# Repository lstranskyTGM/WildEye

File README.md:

# WildEye

WIldEye Wildkamera Diplomprojekt

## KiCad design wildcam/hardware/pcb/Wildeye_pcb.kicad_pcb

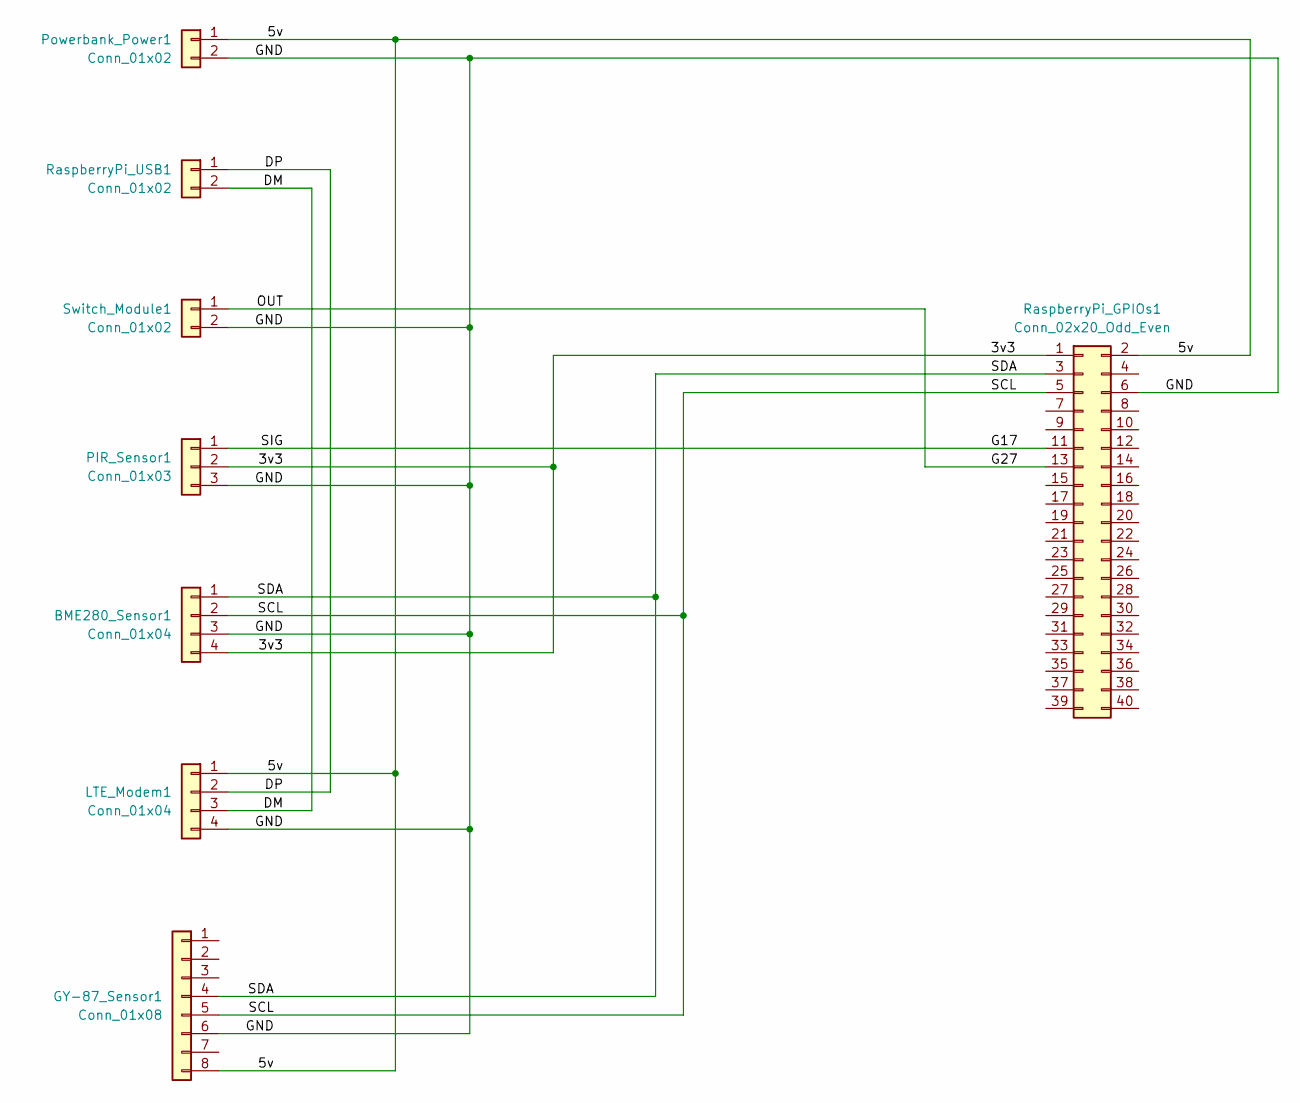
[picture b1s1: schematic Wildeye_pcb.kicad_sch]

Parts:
BME280_Sensor1: Conn_01x04; PinHeader_1x04_P2.54mm_Vertical
GY-87_Sensor1: Conn_01x08; PinHeader_1x08_P2.54mm_Vertical
LTE_Modem1: Conn_01x04; PinHeader_1x04_P2.54mm_Vertical
PIR_Sensor1: Conn_01x03; PinHeader_1x03_P2.54mm_Vertical
Powerbank_Power1: Conn_01x02; PinHeader_1x02_P2.54mm_Vertical
RaspberryPi_GPIOs1: Conn_02x20_Odd_Even; PinHeader_2x20_P2.54mm_Vertical
RaspberryPi_USB1: Conn_01x02; PinHeader_1x02_P2.54mm_Vertical
Switch_Module1: Conn_01x02; PinHeader_1x02_P2.54mm_Vertical

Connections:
/3v3: BME280_Sensor1.4, PIR_Sensor1.2, RaspberryPi_GPIOs1.1
/5v: GY-87_Sensor1.8, LTE_Modem1.1, Powerbank_Power1.1 (5V), RaspberryPi_GPIOs1.2
/DM: LTE_Modem1.3, RaspberryPi_USB1.2
/DP: LTE_Modem1.2, RaspberryPi_USB1.1
/G17: PIR_Sensor1.1, RaspberryPi_GPIOs1.11
/G27: RaspberryPi_GPIOs1.13, Switch_Module1.1
/GND: BME280_Sensor1.3, GY-87_Sensor1.6, LTE_Modem1.4, PIR_Sensor1.3, Powerbank_Power1.2 (GND), RaspberryPi_GPIOs1.6, Switch_Module1.2
/SCL: BME280_Sensor1.2, GY-87_Sensor1.5, RaspberryPi_GPIOs1.5
/SDA: BME280_Sensor1.1, GY-87_Sensor1.4, RaspberryPi_GPIOs1.3

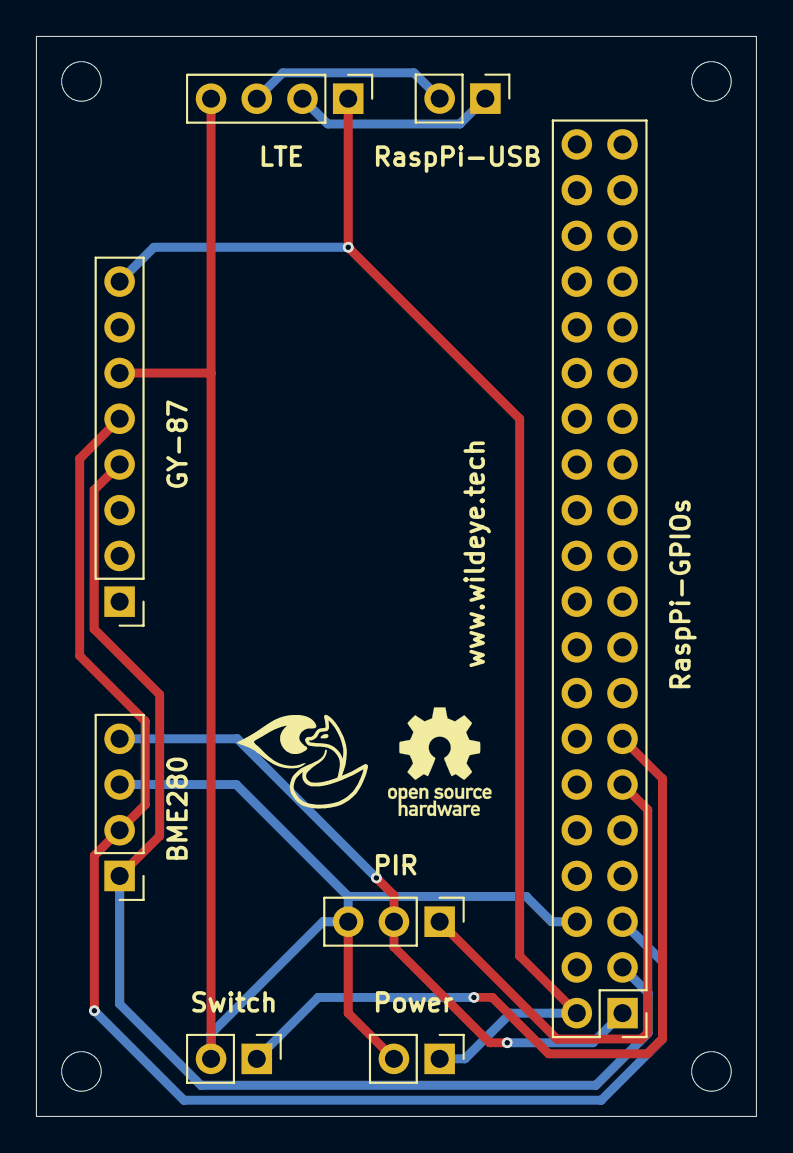
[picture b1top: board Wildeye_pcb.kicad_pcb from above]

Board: 2 copper layers, 40.0 x 60.0 mm, 12 parts (0 on the bottom side), 9 nets.

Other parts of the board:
REF1, REF2, REF3, REF4: MountingHole_2.2mm_M2

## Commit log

2024-09-30 upated ReadMe.md
2024-09-30 added project representation website v1
2024-10-04 added main website
2024-10-04 added dashboard v1
2024-10-04 fixed dependency issues
2024-10-07 slightly changed layout, disabled zoom control for map.
2024-10-08 added add camera button and modal, edit icon, slight layout changes
2024-10-16 Add project directories and placeholder files
2024-10-18 Revise project folder structure
2024-10-18 Unify .gitignore files
2024-10-21 Create test_bme280_sensor.py for temperature, humidity, and pressure data
2024-10-22 Create test_bh1750_sensor.py for light intensity data
2024-10-23 Switch test_bme280_sensor.py to smbus from busio
2024-10-23 Switch test_pir_sensor.py to RPi.GPIO library from gpiozero
2024-10-23 Enhance test_camera_module.py with improved error handling and modular design
2024-10-23 Misc: update code style and comments
2024-10-23 Create LICENSE
2024-10-24 changed layout slightly, changed names to be more consistent.
2024-10-24 added updates for current status
2024-10-25 Create test_ds3231.py for reading and setting time
2024-10-26 Improve test_pir_sensor.py overall error handling
2024-10-26 Enhance: improve error handling across all test scripts
2024-10-26 Modify test_ds3231_rtc.py set_time conversion logic
2024-10-28 Resolve naming issue in test_bh1750_sensor.py
2024-10-29 Create test_mpu6050_sensor.py for accelerometer and gyroscope data
2024-10-30 Create test_flask_app/ for Flask-based configuration interface
2024-11-01 Misc: add error prints, rename vars, PEP8 fixes, remove .gitkeep
2024-11-03 Create folder structure for test scripts
2024-11-07 Create test_background_subtraction.py for presence detection
2024-11-08 added random pixabay pictures, new logo
2024-11-13 new logo
2024-11-13 added v1 of api design
2024-11-14 small change to api
2024-11-19 Strapi Prototyping
2024-11-26 added new news to news section
2024-11-27 Remove test_background_subtraction.py: not used
2024-11-29 added material web components, css variables.
2024-12-01 Create test_lte_modem.py for AT command interface
2024-12-02 Changed Dashboard to match material design mockup.
2024-12-03 Create test_optical_flow.py for motion detection
2024-12-04 changed title and favicon, changed MapView to match Mockup.
2024-12-04 Notes for AI
2024-12-04 Remove test_bh1750_sensor.py: not used
2024-12-04 Remove .gitkeep
2024-12-05 account view
2024-12-08 Mac projekt hinzu gefügt
2024-12-08 Create settings.md for configuration options
2024-12-09 changed AccountView.vue, added CameraComponent.vue stuff
2024-12-09 Modify settings.md: updated variable names and datatypes for consistency
2024-12-11 Projektwebsite v2 fertig
2024-12-12 updated marker popup component to new material design
2024-12-13 Neues Update
2024-12-13 Erstellen des Diagrammes des neuronaln Netwerkes.
2024-12-13 Modify wildcam.conf: add settings for device configuration
2024-12-13 Create network.conf for LTE and server connection settings
2024-12-19 added new color schemes, temp dialog eventually used for settings and camera-code input
2024-12-19 small api design update, advanced settings dialog added
2024-12-31 Move test_pir_sensor.py to detection folder
2024-12-31 Rename test_lte_modem.py to test_lte_at.py
2024-12-31 Create test_lte_gps.py for GPS location retrieval
2025-01-01 Modify test_pir_sensor.py: modularize, simplify, fix interrupts
2025-01-02 Modify test_bme280_sensor.py: implement class, add logging, improve documentation
2025-01-03 Modify test_mpu6050_sensor.py: implement class/library, add logging, improve documentation
2025-01-03 Remove test_ds3231_rtc.py: critical functionality issues, not feasible to fix
2025-01-05 Create test_http_request.py for HTTP requests over LTE
2025-01-08 small design updates
2025-01-08 added popout image viewer
2025-01-08 small design changes in the account view
2025-01-09 small design and layout changes throughout whole website
2025-01-10 started implementing future API, currently using development test server with default values
2025-01-11 added new API functionality, changed layout of settings popups.
2025-01-14 added new updates, portraits, changes milestone completion
2025-01-14 css updates for projektwebseite
2025-01-14 datum geändert auf heutiges
2025-01-19 added login, logout procedure, cookies for session storage.
2025-01-19 additional session logic, small design updates
2025-01-20 added docker and new leo bild
2025-01-22 updated api design, small changes in code to adapt.
2025-01-22 added flask api server to git
2025-01-23 Add STL files for prototype to wildcam/hardware/3d_models folder
2025-01-27 Fix docker-compose.yml: add restart policy
2025-02-11 updated project website
2025-02-11 changed image to a cc image.
2025-02-17 Move manual test scripts to /scripts/tests/manual/
2025-02-17 Create README.md
    An API documentation V1
2025-02-17 small format changes to README.md
2025-02-17 Update README.md
    fixed typos in requests
2025-02-18 updated logo, api now works for login and getCameras
2025-02-18 replaced camera quick info with actual info from api
2025-02-18 added code for carousel of standard and AI analyzed image, replaced logo with new version
2025-02-18 Create base_module.py: abstract base class for hardware modules
2025-02-19 Create media/ folder structure for storing captured data
2025-02-19 Create camera_module.py: implement image & video capture
2025-02-20 Modify base_module.py: add type hinting
2025-02-20 Fix camera_module.py: ensure camera stops after recording
2025-02-21 Modify base_module.py: improve docs & remove unused read_data method
2025-02-21 Modify camera_module.py: refine docs & cleanup method
2025-02-21 Create pir_sensor.py: handle motion detection using GPIO
2025-02-23 Modify docstring formatting for scripts under /hardware
2025-02-23 Refactor initialize to hardware_setup & update wrapper calls for clarity
2025-02-23 Modify generate_file_path in camera_module.py to be private for internal use
2025-02-23 Create event_handler.py: handle motion events & trigger media capture
2025-02-24 new updates for project website
2025-02-24 Fix event_handler.py: resolve TypeError by correcting handle_motion_event parameter
2025-02-24 Refactor event_handler.py: move record_type to init as a temporary fixed value
2025-02-24 Modify event_handler.py: enhance docstrings & define future methods
2025-02-24 Create wildcam.py: initialize system and set up event handling
2025-02-25 Create main.py: initialize and start WildCam system with safe shutdown
2025-02-25 Fix missing init.py in core folder to enable module imports
2025-02-25 added dockerfile for webapp, small changes in map, login/logout, and picture logic
2025-02-26 Add logos to branding/ and remove .gitkeep files
2025-02-26 fix(webapp): change exposed port in docker-compose to avoid conflict
2025-02-28 refactor(base_module): rename _initialized to _hardware_configured
2025-03-01 updates in api integration, 3 hours of debugging only to settle on an unsatisfactory solution. might be a huge security risk, but who cares
2025-03-01 forgot to remove some debugging stuff
2025-03-01 added new update to projektwebseite
2025-03-04 feat(pcb): upload PCB design, gerber, and drill files
2025-03-04 added new API connectivity, hearted function, and auto-icon functionality for tags
2025-03-06 chore(deps): freeze libraries and save to requirements.txt
2025-03-07 fix(event_handler): initialize & clean up hardware modules properly
2025-03-07 fix(main): avoid UnboundLocalError if WildCam initialization fails
2025-03-07 refactor(event_handler): rename set_interrupts to set_events for clarity
2025-03-07 refactor(event_handler): rename camera to camera_module for consistency
2025-03-07 Update AI: best.pt; main.py und test.py hinzugefügt
    Update AI: best.pt; main.py und test.py hinzugefügt
2025-03-07 added image search and filter functionality, fixed camera settings API connection.
2025-03-07 update: test.py
    update: test.py
2025-03-07 draft for pulling images from the api and analyzing it
2025-03-07 appropriate gitignore
2025-03-07 finished AI-API connection and automatic analysis
2025-03-07 start guide + restructuring
2025-03-08 chore(deps): remove misplaced requirements.txt from root folder
2025-03-08 fix(main): update event_handler calls to match renaming
2025-03-08 refactor(wildcam): move cleanup logic from main to wildcam & add method docs
2025-03-08 test(test_file_upload): add script for testing file upload to API
2025-03-09 Dockerfile for AI Bilderkennung
2025-03-09 fix(camera_module): adjust file path & move directory creation logic
2025-03-09 fix(camera_module): ensure camera is closed on error
2025-03-09 update: train.py hinzugefügt
    update: train.py hinzugefügt
2025-03-09 update: Bildklassifizierungs-code hinzugefügt; test-Klasse für Yolo hinzugefügt
    update: Bildklassifizierungs-code hinzugefügt; test-Klasse für Yolo hinzugefügt
2025-03-09 update: Speispie-Code hinzugefügt
    update: Speispie-Code hinzugefügt
2025-03-09 feat(api_client): add HTTP client for API requests
2025-03-10 feat(api_client): add upload_file method for multipart requests
2025-03-10 feat(strapi_service): add service for Strapi API integration
2025-03-10 fix(network): add missing __init__.py file
2025-03-10 fix(camera_module): correct file path to prevent permission error
2025-03-10 feat(media): adjust folder structure with images and videos subfolders
2025-03-10 feat(upload_manager): add service for managing file upload queue
2025-03-11 feat(wildcam): add scheduled update cycles using threading timer
2025-03-11 feat(event_handler): implement update cycle functionality
2025-03-11 fix(upload_manager): handle list response from Strapi API
2025-03-11 chore(scripts): add .gitignore for software solution folder
2025-03-11 Add Model_v4.py via file upload
2025-03-11 ability to change name, small design changes
2025-03-13 small changes to almost everything for medt ek
2025-03-13 added pwa manifest
2025-03-20 changed icons, optimised layouts for mobile
2025-03-21 chore(scripts): update .gitignore with excluded folders
2025-03-21 feat(3d_models): add wildeye-v1.0 .stl files and images
2025-06-06 added new updates, slightly changes layout to fit mobile view better
2025-06-06 added logo updated retroactively
2025-06-06 fix(docker-compose): update vue-app port mapping to available 8090
2025-06-06 feat(website): update 3d-model image to v1.0
2025-12-15 build(deps-dev): bump node-forge from 1.3.1 to 1.3.3 in /Projektwebseite
    Bumps [node-forge](https://github.com/digitalbazaar/forge) from 1.3.1 to 1.3.3.
    - [Changelog](https://github.com/digitalbazaar/forge/blob/main/CHANGELOG.md)
    - [Commits](https://github.com/digitalbazaar/forge/compare/v1.3.1...v1.3.3)
    ---
    updated-dependencies:
    - dependency-name: node-forge
